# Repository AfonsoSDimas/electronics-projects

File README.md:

📡 Electronics Projects Lab

1. Visão geral

Este repositório agrega um conjunto de projetos de eletrónica analógica, digital, mista e sistemas embebidos, cobrindo todo o ciclo de desenvolvimento de engenharia, desde a conceção teórica e modelação matemática até à implementação em hardware, firmware e validação experimental.

A organização do repositório segue boas práticas académicas e industriais, com foco em:

  -Clareza estrutural
  -Reprodutibilidade técnica
  -Documentação rigorosa
  -Separação entre teoria, simulação e implementação

2. Âmbito técnico

Os projetos aqui incluídos podem abranger, entre outros, os seguintes domínios:
  
  -Eletrónica analógica e digital
  -Circuitos mistos (mixed-signal)
  -Osciladores, filtros e amplificadores
  -Sistemas embebidos (microcontroladores, ESP32, Arduino, bare-metal)
  -Simulação elétrica SPICE
  -Design de PCB (2 camadas, 4 camadas, alta velocidade)
  -Aquisição e análise de sinais
  -Comparação entre simulação e medições reais

3. Ferramentas e tecnologias utilizadas

Dependendo do projeto, poderão ser utilizadas as seguintes ferramentas:

  -KiCad – esquemáticos e layout PCB
  -LTspice / NGspice – simulação elétrica
  -Python / MATLAB / Octave – cálculos, modelação e análise
  -C / C++ / MicroPython – firmware
  -Osciloscópio, analisador lógico – validação experimental

4. Metodologia de desenvolvimento

Cada projeto segue, sempre que aplicável, a seguinte metodologia:

  -Definição do problema e requisitos
  -Fundamentação teórica e cálculos
  -Simulação elétrica
  -Desenho do esquemático
  -Layout e fabrico de PCB
  -Desenvolvimento de firmware
  -Testes experimentais e validação
  -Documentação final
  
Esta abordagem visa garantir consistência, rastreabilidade e rigor técnico.

5. Nota final

Este repositório destina-se tanto a fins académicos como a portfólio técnico profissional, refletindo uma abordagem de engenharia completa, fundamentada e verificável.

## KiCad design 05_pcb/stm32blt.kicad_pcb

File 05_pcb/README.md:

Agrupa todos os ficheiros relacionados com o layout de PCB e preparação para fabrico, incluindo Gerbers, ficheiros de furação e montagem.

Esta pasta reflete a transição do modelo teórico para implementação física.

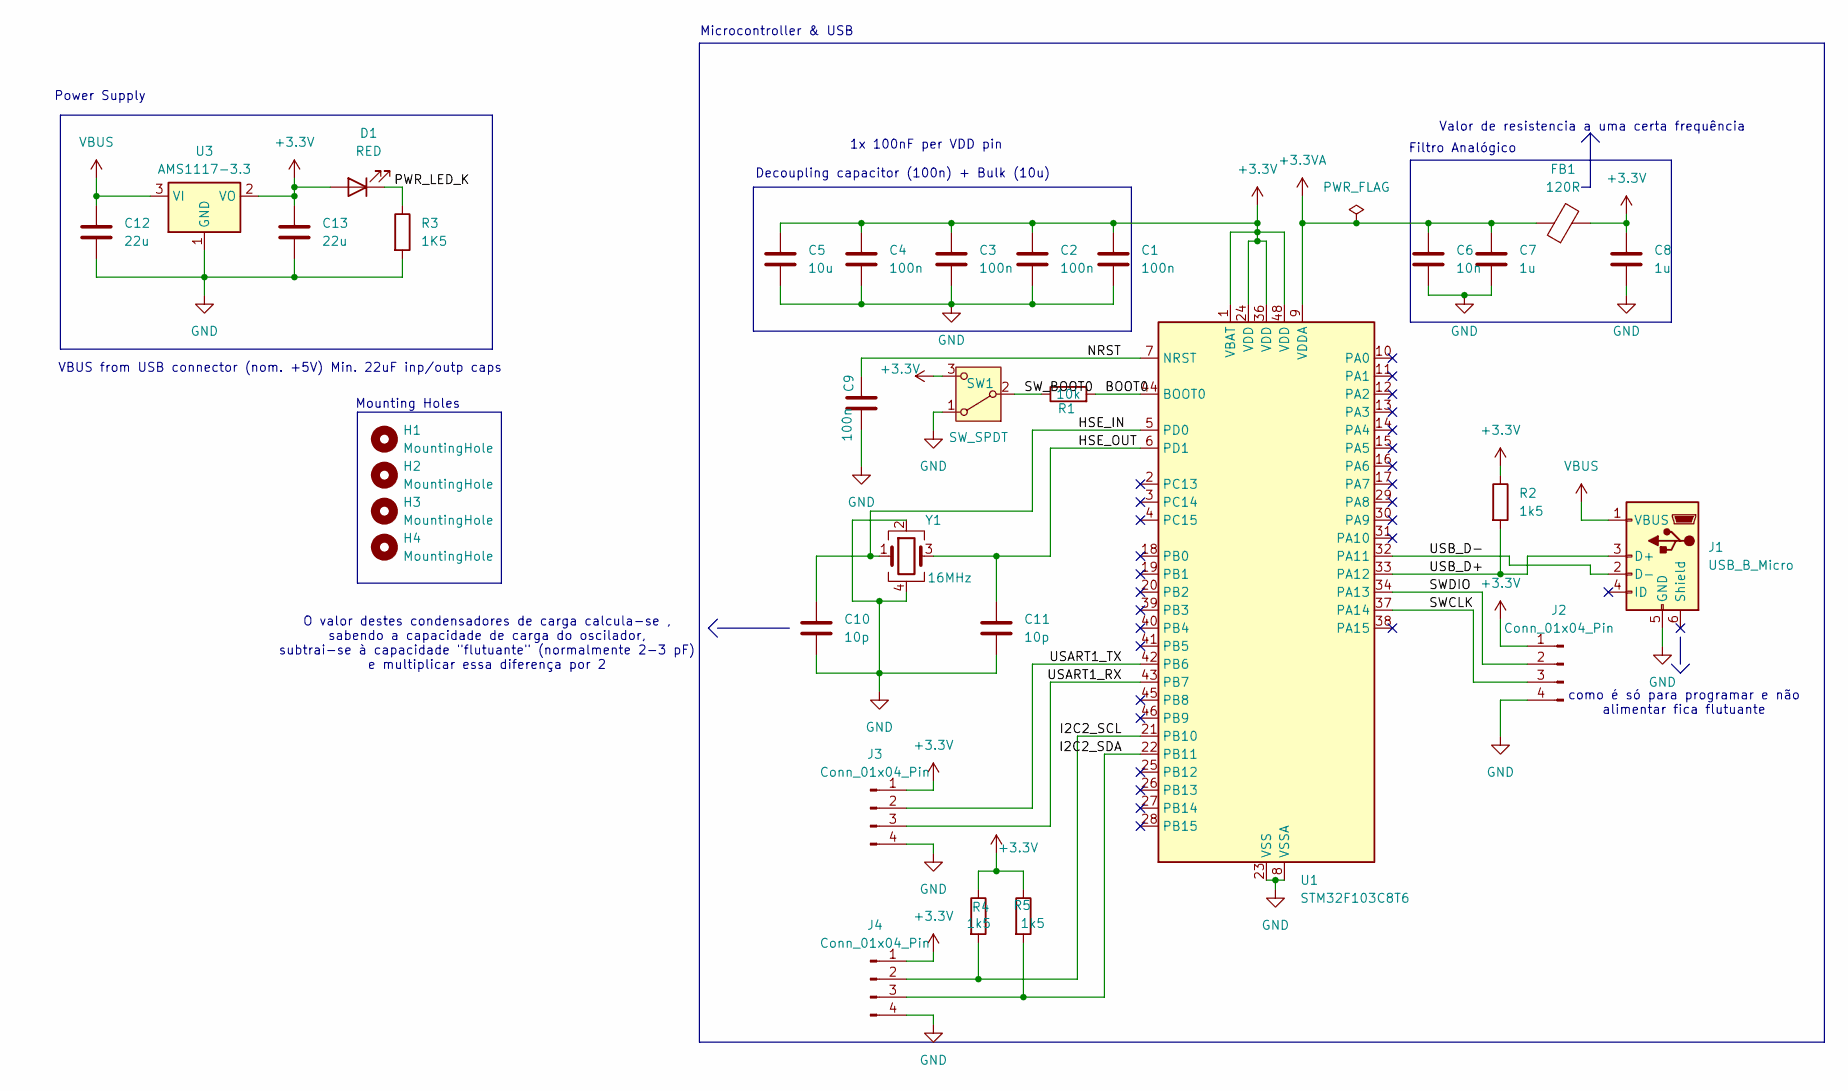
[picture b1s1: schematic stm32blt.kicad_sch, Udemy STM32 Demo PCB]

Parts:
C1, C2, C3, C4: 100n; C_0603_1608Metric_Pad1.08x0.95mm_HandSolder
C5: 10u; C_0603_1608Metric_Pad1.08x0.95mm_HandSolder
C6: 10n; C_0402_1005Metric_Pad0.74x0.62mm_HandSolder
C7, C8: 1u; C_0402_1005Metric_Pad0.74x0.62mm_HandSolder
C9: 100n; C_0402_1005Metric_Pad0.74x0.62mm_HandSolder
C10, C11: 10p; C_0402_1005Metric_Pad0.74x0.62mm_HandSolder
C12, C13: 22u; C_0805_2012Metric_Pad1.18x1.45mm_HandSolder
D1: RED; LED_0603_1608Metric_Pad1.05x0.95mm_HandSolder
FB1: 120R; L_0603_1608Metric_Pad1.05x0.95mm_HandSolder
H1, H2, H3, H4: MountingHole; MountingHole_2.2mm_M2
J1: USB_B_Micro; USB_Micro-B_Wuerth_629105150521
J2, J3, J4: Conn_01x04_Pin; PinHeader_1x04_P2.54mm_Vertical
R1: 10k; R_0402_1005Metric_Pad0.72x0.64mm_HandSolder
R2, R4, R5: 1k5; R_0402_1005Metric_Pad0.72x0.64mm_HandSolder
R3: 1K5; R_0402_1005Metric_Pad0.72x0.64mm_HandSolder
SW1: SW_SPDT; SW_SPDT_PCM12
U1: STM32F103C8T6; LQFP-48_7x7mm_P0.5mm
U3: AMS1117-3.3; SOT-223-3_TabPin2
Y1: 16MHz; Crystal_SMD_3225-4Pin_3.2x2.5mm_HandSoldering

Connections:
+3.3V: C1.1, C2.1, C3.1, C4.1, C5.1, C8.1, C13.1, D1.2 (A), FB1.2, J2.1, J3.1, J4.1, R2.1, R4.1, R5.1, SW1.3 (C), U1.1 (VBAT), U1.24 (VDD), U1.36 (VDD), U1.48 (VDD), U3.2 (VO)
+3.3VA: C6.1, C7.1, FB1.1, U1.9 (VDDA)
/BOOT0: R1.2, U1.44 (BOOT0)
/HSE_IN: C10.1, U1.5 (PD0), Y1.1
/HSE_OUT: C11.1, U1.6 (PD1), Y1.3
/I2C2_SCL: J4.2, R4.2, U1.21 (PB10)
/I2C2_SDA: J4.3, R5.2, U1.22 (PB11)
/NRST: C9.2, U1.7 (NRST)
/PWR_LED_K: D1.1 (K), R3.1
/SWCLK: J2.3, U1.37 (PA14)
/SWDIO: J2.2, U1.34 (PA13)
/SW_BOOT0: R1.1, SW1.2 (B)
/USART1_RX: J3.3, U1.43 (PB7)
/USART1_TX: J3.2, U1.42 (PB6)
/USB_D+: J1.3 (D+), R2.2, U1.33 (PA12)
/USB_D-: J1.2 (D-), U1.32 (PA11)
GND: C1.2, C2.2, C3.2, C4.2, C5.2, C6.2, C7.2, C8.2, C9.1, C10.2, C11.2, C12.2, C13.2, J1.5 (GND), J2.4, J3.4, J4.4, R3.2, SW1.1 (A), U1.8 (VSSA), U1.23 (VSS), U1.35 (VSS), U1.47 (VSS), U3.1 (GND), Y1.2, Y1.4
VBUS: C12.1, J1.1 (VBUS), U3.3 (VI)

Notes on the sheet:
Microcontroller & USB
Mounting Holes
1x 100nF per VDD pin
O valor destes condensadores de carga calcula-se , sabendo a capacidade de carga do oscilador, subtrai-se à capacidade "flutuante" (normalmente 2-3 pF) e multiplicar essa diferença por 2
Filtro Analógico
Valor de resistencia a uma certa frequência
VBUS from USB connector (nom. +5V) Min. 22uF inp/outp caps
Decoupling capacitor (100n) + Bulk (10u)
como é só para programar e não alimentar fica flutuante
Power Supply

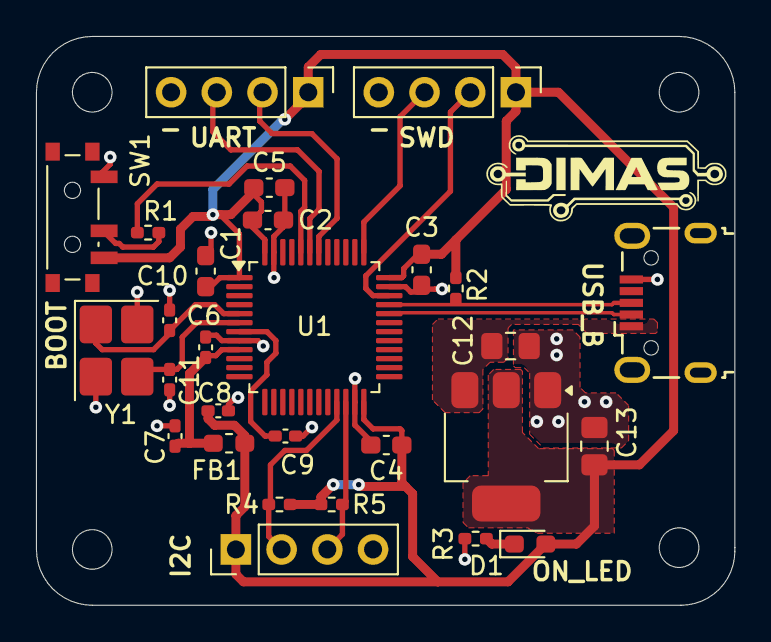
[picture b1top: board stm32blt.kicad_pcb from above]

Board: 2 copper layers, 38.8 x 31.6 mm, 32 parts (0 on the bottom side), 18 nets.

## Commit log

2026-01-31 Create LICENSE
2026-01-31 Create 1st
2026-01-31 Update and rename 1st to Description
2026-01-31 Update 1st
2026-01-31 Rename 1st to Descripition
2026-01-31 Esquematico stm32
2026-01-31 PCB do stm32
2026-01-31 Foto do esquematico do stm32
2026-01-31 Foto do PCB do stm32
2026-01-31 Rename 08_images/Screenshot 2026-01-31 145844.png to 08_images/stm32blt/Screenshot 2026-01-31 145844.png
2026-01-31 Rename 08_images/Screenshot 2026-01-31 145935.png to 08_images/stm32blt/Screenshot 2026-01-31 145935.png
2026-01-31 Moved folder
2026-01-31 Kicad file para stm32
2026-01-31 Rename Description to README.md
2026-01-31 Rename Descripition to README.md
2026-01-31 Rename LICENSE to LICENSE.md
2026-02-01 Pastas do projeto drone
2026-02-01 DataSheets update
2026-02-01 AMS1117 DataSheet
2026-02-01 Pasta para partes dos projetos
2026-02-01 nRF8001 DataSheet (Bluethoot Low Power Chip)
2026-02-02 32.768 kHz Crystal for Bluethoot Low Energy
2026-02-02 ECX-1637B2 DataSheet 16MhZ Crystal
2026-02-02 AN4488 Application Note for the STM32
2026-02-04 Drone Kicad file and schematic photo
2026-02-05 SMBJ24CA DataSheet TVS Diode
2026-02-05 Screenshots of schematic and updated the schematic file
2026-02-11 nRF8001 DataSheet
2026-02-11 Battery IC's Datasheets
2026-02-12 Kicad Zip
2026-02-12 Footprints & 3D Models
2026-02-12 AN043 - How to make a trace antenna
